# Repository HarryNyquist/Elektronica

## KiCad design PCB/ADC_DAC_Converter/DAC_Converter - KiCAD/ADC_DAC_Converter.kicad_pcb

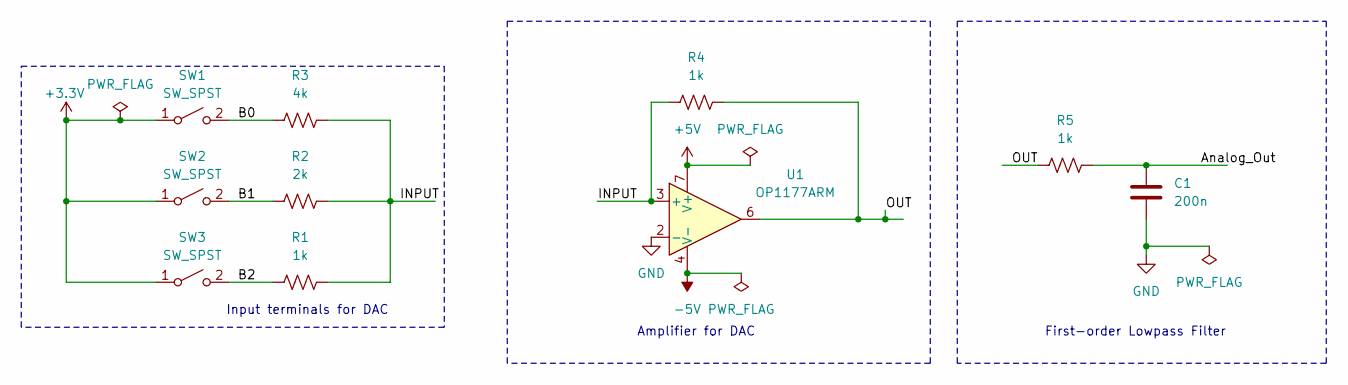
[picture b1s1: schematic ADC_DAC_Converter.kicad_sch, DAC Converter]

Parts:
C1: 200n; C_Axial_L3.8mm_D2.6mm_P7.50mm_Horizontal
R1, R4, R5: 1k; R_Axial_DIN0207_L6.3mm_D2.5mm_P15.24mm_Horizontal
R2: 2k; R_Axial_DIN0207_L6.3mm_D2.5mm_P15.24mm_Horizontal
R3: 4k; R_Axial_DIN0207_L6.3mm_D2.5mm_P15.24mm_Horizontal
SW1, SW2, SW3: SW_SPST; SW_DIP_SPSTx01_Slide_6.7x4.1mm_W7.62mm_P2.54mm_LowProfile
U1: OP1177ARM; MSOP-8_3x3mm_P0.65mm

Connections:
+3.3V: SW1.1 (A), SW2.1 (A), SW3.1 (A)
+5V: U1.7 (V+)
-5V: U1.4 (V-)
/Analog_Out: C1.1, R5.2
/B0: R3.1, SW1.2 (B)
/B1: R2.1, SW2.2 (B)
/B2: R1.1, SW3.2 (B)
/INPUT: R1.2, R2.2, R3.2, R4.1, U1.3 (+)
/OUT: R4.2, R5.1, U1.6
GND: C1.2, U1.2 (-)

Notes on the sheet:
Input terminals for DAC
First-order Lowpass Filter
Amplifier for DAC

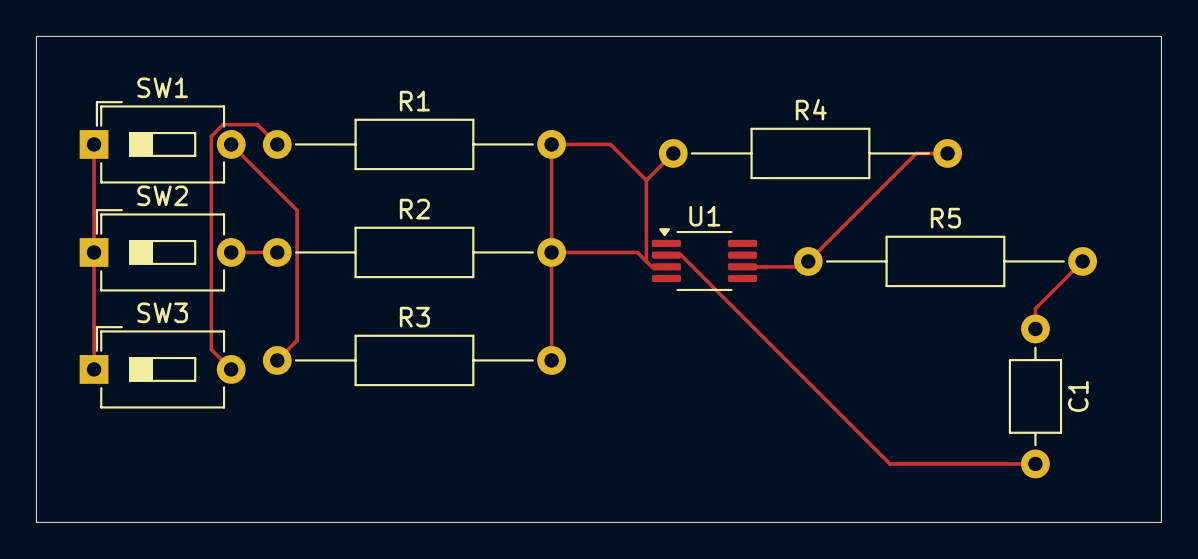
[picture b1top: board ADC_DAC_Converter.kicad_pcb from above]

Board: 2 copper layers, 62.5 x 27.0 mm, 10 parts (0 on the bottom side), 8 nets.

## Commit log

2024-06-27 Convolution done!
2024-06-28 FFT with correct frequency plotted, filtering yet to be done
2024-06-28 Reduced noise but sound slightly muffled
2024-06-29 Well made bandpass filter, only need to remove 2 beeps out of 6
2024-06-29 Removed all spikes except one, implemented bandpass butterworth filter(excellent filter btw)
2024-06-29 Fully works! Will experiment with amplitude later
2024-06-30 Added documentation
2024-07-03 Added PCB Schematic, PCB design yet to be completed
2024-07-03 PCB Design Completed
2024-07-03 Documentation for PCB over, power rating yet to be updated
2024-07-07 Repo not yet public, power rating added
